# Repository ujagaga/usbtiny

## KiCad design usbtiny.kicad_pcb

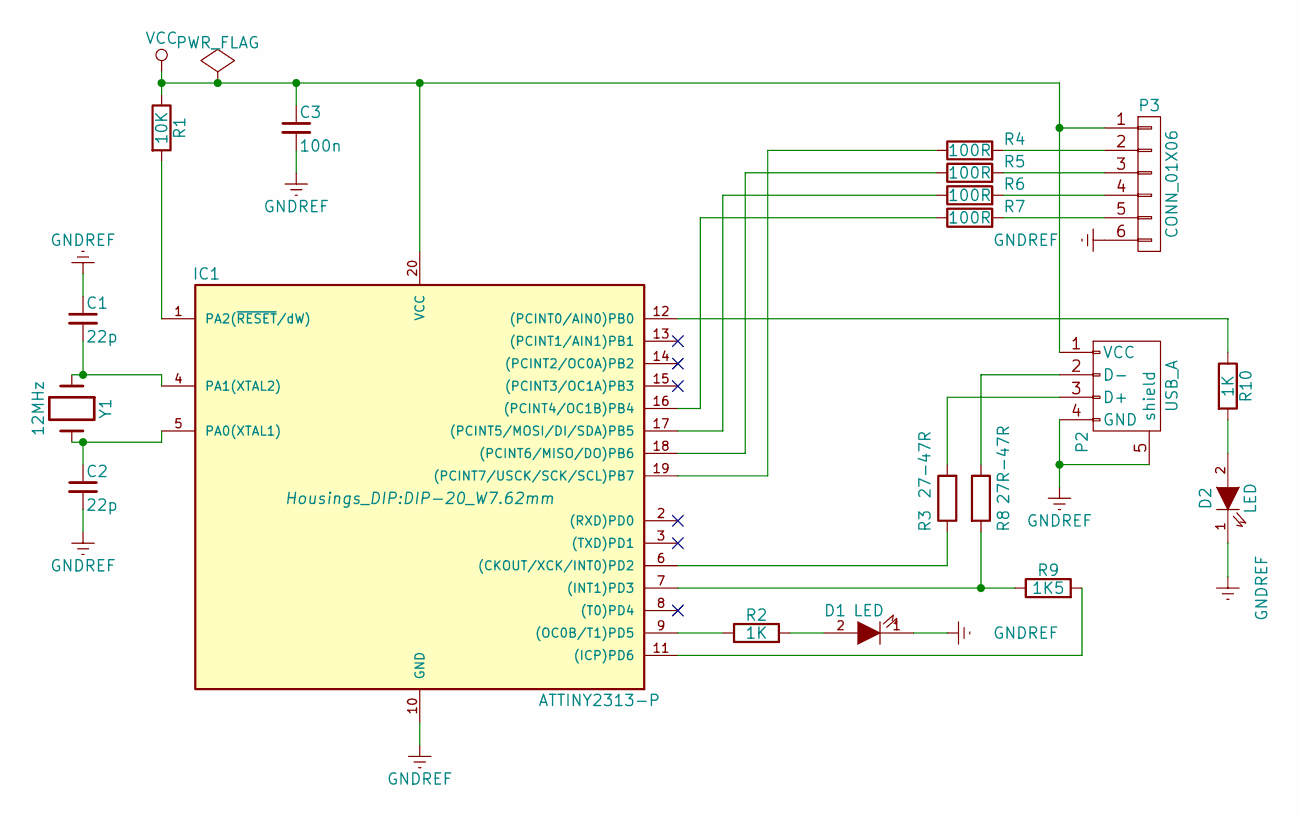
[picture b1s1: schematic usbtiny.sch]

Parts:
C1, C2: 22p; C_1206_HandSoldering
C3: 100n; C_1206_HandSoldering
D1, D2: LED; LED_0805
IC1: ATTINY2313-P; DIP-20_W7.62mm
P2: USB_A
P3: CONN_01X06; Pin_Header_Straight_1x06
R1: 10K; R_0805
R2, R10: 1K; R_0805
R3: 27-47R; R_0805
R4, R5, R6, R7: 100R; R_0805
R8: 27R-47R; R_0805
R9: 1K5; R_0805
Y1: 12MHz; Crystal_HC49-U_Vertical

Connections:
GNDREF: C1.1, C2.2, C3.2, D1.1 (K), D2.1 (K), IC1.10 (GND), P2.4 (GND), P2.5 (shield), P3.6
unnamed: C1.2, IC1.4 (PA1(XTAL2)), Y1.1
unnamed: C2.1, IC1.5 (PA0(XTAL1)), Y1.2
unnamed: D1.2 (A), R2.2
unnamed: D2.2 (A), R10.2
unnamed: IC1.1 (PA2(~RESET~/dW)), R1.2
unnamed: IC1.6 ((CKOUT/XCK/INT0)PD2), R3.1
unnamed: IC1.7 ((INT1)PD3), R8.2, R9.1
unnamed: IC1.9 ((OC0B/T1)PD5), R2.1
unnamed: IC1.11 ((ICP)PD6), R9.2
unnamed: IC1.12 ((PCINT0/AIN0)PB0), R10.1
unnamed: IC1.16 ((PCINT4/OC1B)PB4), R7.1
unnamed: IC1.17 ((PCINT5/MOSI/DI/SDA)PB5), R6.1
unnamed: IC1.18 ((PCINT6/MISO/DO)PB6), R5.1
unnamed: IC1.19 ((PCINT7/USCK/SCK/SCL)PB7), R4.1
unnamed: P2.2 (D-), R8.1
unnamed: P2.3 (D+), R3.2
unnamed: P3.2, R4.2
unnamed: P3.3, R5.2
unnamed: P3.4, R6.2
unnamed: P3.5, R7.2
VCC: C3.1, IC1.20 (VCC), P2.1 (VCC), P3.1, R1.1

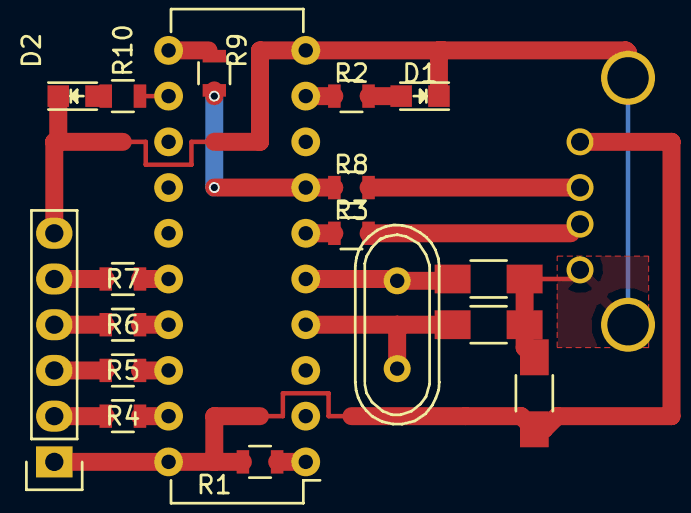
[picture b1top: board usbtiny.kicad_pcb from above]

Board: 2 copper layers, 19 parts (1 on the bottom side), 22 nets.

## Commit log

2016-10-21 * Added png schematic and PCB * Added Attiny hex image and flash script
2016-10-22 Reduced the PCB size
2016-10-22 Added pin labels in a doc file so you can print it and glue it to the PCB
